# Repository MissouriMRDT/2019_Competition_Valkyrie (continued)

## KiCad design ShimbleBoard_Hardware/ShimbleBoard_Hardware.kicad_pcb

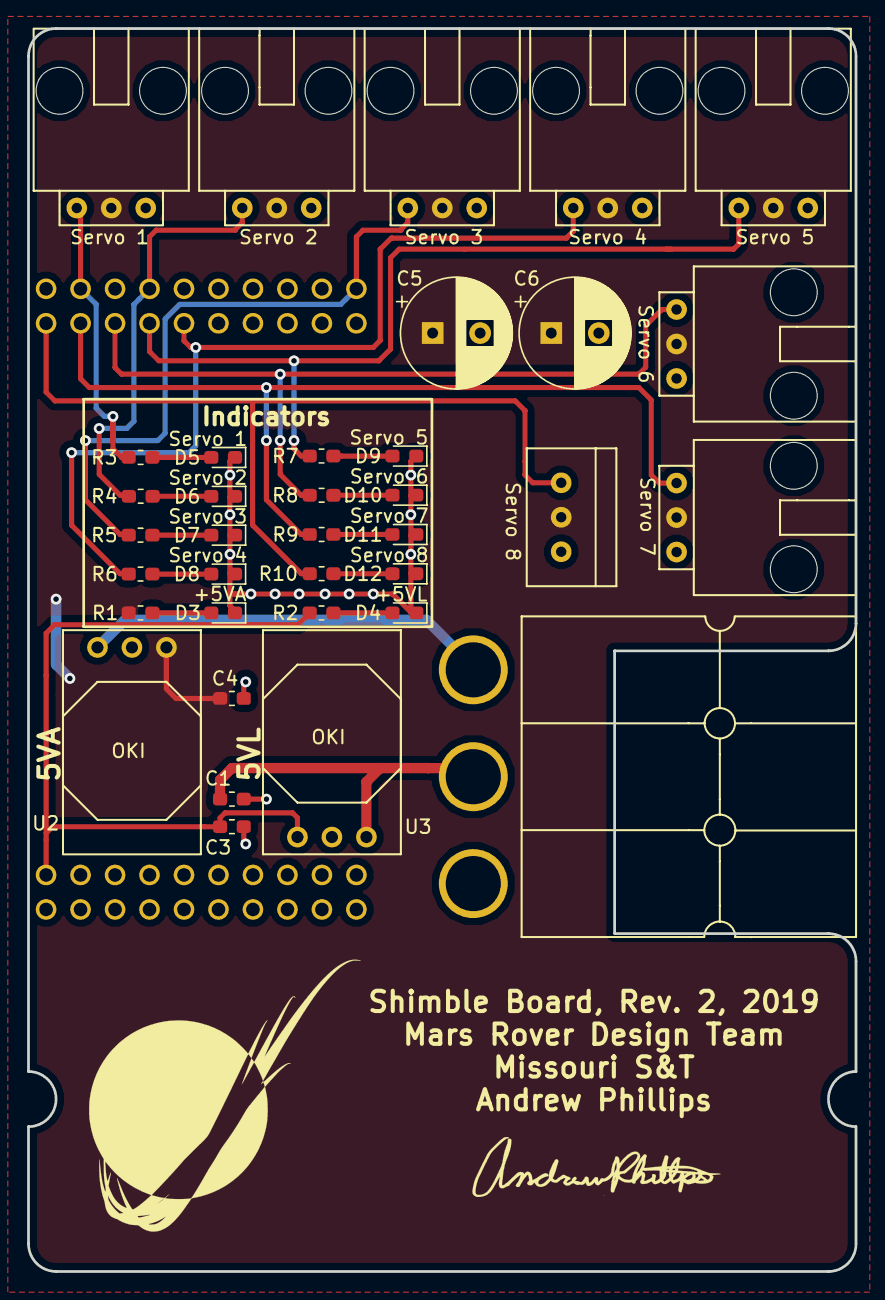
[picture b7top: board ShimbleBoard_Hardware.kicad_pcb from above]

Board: 2 copper layers, 61.0 x 91.6 mm, 38 parts (1 on the bottom side), 23 nets.

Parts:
C1, C2, C3, C4: 10uF; C_0603_1608Metric_Pad1.05x0.95mm_HandSolder
C5, C6: 470u; CP_Radial_D8.0mm_P3.50mm
Conn1: AndersonPP; Anderson_3_Horizontal_Side_by_Side
Conn2, Conn3, Conn4, Conn5, Conn6, Conn7, Conn8: Molex_SL_03; MOLEX_SL_03_Horizontal
Conn9: Molex_SL_03; MOLEX_SL_03_Vertical
D3: 5V_Act_LED; D_0603_1608Metric_Pad1.05x0.95mm_HandSolder
D4: 5V_Log_LED; D_0603_1608Metric_Pad1.05x0.95mm_HandSolder
D5: Ctrl_1_LED; D_0603_1608Metric_Pad1.05x0.95mm_HandSolder
D6: Ctrl_2_LED; D_0603_1608Metric_Pad1.05x0.95mm_HandSolder
D7: Ctrl_3_LED; D_0603_1608Metric_Pad1.05x0.95mm_HandSolder
D8: Ctrl_4_LED; D_0603_1608Metric_Pad1.05x0.95mm_HandSolder
D9: Ctrl_5_LED; D_0603_1608Metric_Pad1.05x0.95mm_HandSolder
D10: Ctrl_6_LED; D_0603_1608Metric_Pad1.05x0.95mm_HandSolder
D11: Ctrl_7_LED; D_0603_1608Metric_Pad1.05x0.95mm_HandSolder
D12: Ctrl_8_LED; D_0603_1608Metric_Pad1.05x0.95mm_HandSolder
R1, R2, R3, R4, R5, R6, R7, R8, R9, R10: 500; R_0603_1608Metric_Pad1.05x0.95mm_HandSolder
U1: TM4C129E_Launchpad; TM4C129E_Launchpad_X7_THT_BOTTOM
U2, U3: OKI; OKI_Horizontal

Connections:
+5VA: C4.1, C5.1, C6.1, Conn2.2, Conn3.2, Conn4.2, Conn5.2, Conn6.2, Conn7.2, Conn8.2, Conn9.2, R1.1, U2.3
+5VL: C3.1, R2.1, U1.+5V', U3.3
+12L: C1.1, Conn1.2, U3.1
+12VA: C2.2, Conn1.3, U2.1
GND: C1.2, C2.1, C3.2, C4.2, C5.2, C6.2, Conn1.1, Conn2.3, Conn3.3, Conn4.3, Conn5.3, Conn6.3, Conn7.3, Conn8.3, Conn9.3, D3.1, D4.1, D5.1, D6.1, D7.1, D8.1, D9.1, D10.1, D11.1, D12.1, U1.GND, U2.2, U3.2
unnamed: D3.2, R1.2
unnamed: D4.2, R2.2
unnamed: D5.2, R3.2
unnamed: D6.2, R4.2
unnamed: D7.2, R5.2
unnamed: D8.2, R6.2
unnamed: D9.2, R7.2
unnamed: D10.2, R8.2
unnamed: D11.2, R9.2
unnamed: D12.2, R10.2
Servo_1_Ctrl: Conn2.1, R3.1, U1.PM7
Servo_2_Ctrl: Conn3.1, R4.1, U1.PA7
Servo_3_Ctrl: Conn4.1, R5.1, U1.PM6
Servo_4_Ctrl: Conn5.1, R6.1, U1.PM1
Servo_5_Ctrl: Conn6.1, R7.1, U1.PM0
Servo_6_Ctrl: Conn7.1, R8.1, U1.PK5
Servo_7_Ctrl: Conn8.1, R9.1, U1.PK4
Servo_8_Ctrl: Conn9.1, R10.1, U1.PG1

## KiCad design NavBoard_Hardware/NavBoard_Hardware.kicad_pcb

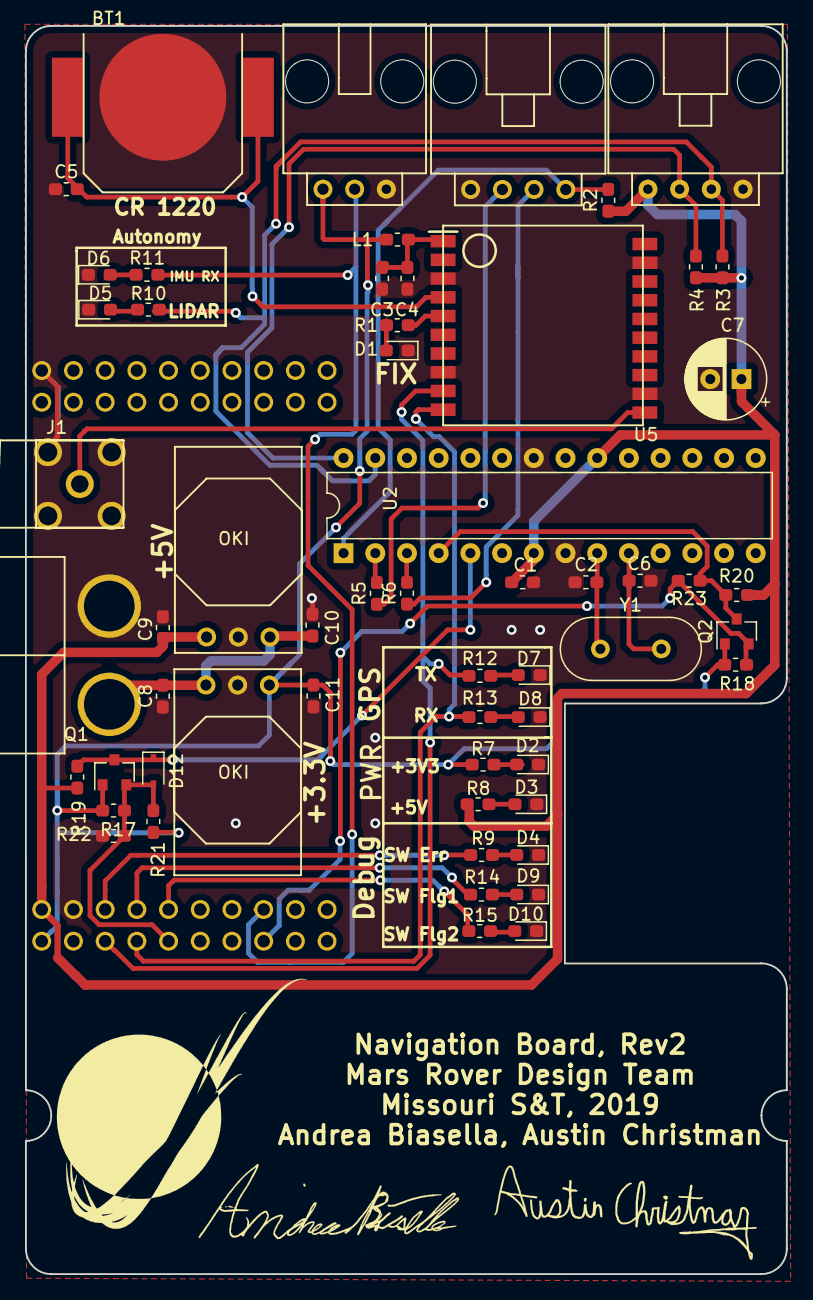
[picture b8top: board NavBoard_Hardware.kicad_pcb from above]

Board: 2 copper layers, 61.0 x 100.0 mm, 59 parts (0 on the bottom side), 37 nets.

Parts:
BT1: Battery_Cell; CR1220_Battery_Holder
C1, C3, C5: 1uF; C_0603_1608Metric_Pad1.05x0.95mm_HandSolder
C2, C6: 22pF; C_0603_1608Metric_Pad1.05x0.95mm_HandSolder
C4: 0.01uF; C_0603_1608Metric_Pad1.05x0.95mm_HandSolder
C7: 680uF; CP_Radial_D6.3mm_P2.50mm
C8, C9, C10, C11: 10u; C_0603_1608Metric_Pad1.05x0.95mm_HandSolder
Conn1: AndersonPP; Anderson_2_Horizontal_Side_by_Side
Conn2: LiDAR; MOLEX_SL_04_Horizontal
Conn3: Molex_SL_03; MOLEX_SL_03_Horizontal
Conn4: Molex_SL_04; MOLEX_SL_04_Horizontal
D1: FIX; LED_0603_1608Metric_Pad1.05x0.95mm_HandSolder
D2, D3, D4, D5, D6, D7, D8, D9, D10: LED; LED_0603_1608Metric_Pad1.05x0.95mm_HandSolder
D12: 1N4148; D_SOD-323
J1: Conn_Coaxial; RP-SMA_Jack_Tru-Hole_Right-Angle
L1: INDUCTOR; L_0603_1608Metric_Pad1.05x0.95mm_HandSolder
Q1, Q2: BSS138; SOT-23
R1, R5, R6: 1K; R_0603_1608Metric_Pad1.05x0.95mm_HandSolder
R2, R17, R18, R19, R20, R21: 10K; R_0603_1608Metric_Pad1.05x0.95mm_HandSolder
R3, R4: 4.7K; R_0603_1608Metric_Pad1.05x0.95mm_HandSolder
R7, R8, R9, R10, R11, R12, R13, R14, R15: 500; R_0603_1608Metric_Pad1.05x0.95mm_HandSolder
R22: 30K; R_0603_1608Metric_Pad1.05x0.95mm_HandSolder
R23: 0; R_0603_1608Metric_Pad1.05x0.95mm_HandSolder
U1: TM4C129E_Launchpad_X9_THT_BOTTOM
U2: ATMEGA328P-Project_Library; DIP-28_W7.62mm
U3, U4: OKI; OKI_Horizontal
U5: FGPMMOPA6H
Y1: Crystal; Crystal_HC49-U_Vertical

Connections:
+3V3: C11.1, Conn3.1, L1.1, Q1.1, Q2.1, R7.1, R17.1, R18.1, R21.1, U1.+3V3, U4.3
+5V: C1.1, C7.1, C9.1, Conn2.1, R2.1, R3.1, R4.2, R8.1, R19.1, R20.1, U1.+5V, U2.7, U2.20, U3.3
/EXAnt: J1.1, U5.11
ATM_RX: Q2.3, R20.2, R23.1, U2.4
ATM_TX: D12.1, Q1.3, R19.2, U2.5
Error_LED: R9.1, U1.PE0
GND: BT1.2, C1.2, C2.2, C3.1, C4.1, C5.2, C6.2, C7.2, C8.2, C9.2, C10.2, C11.2, Conn1.1, Conn2.4, Conn3.3, Conn4.1, D1.1, D2.1, D3.1, D4.1, D5.1, D6.1, D7.1, D8.1, D9.1, D10.1, J1.2, R22.2, U1.GND, U2.8, U2.22, U3.2, U4.2, U5.3, U5.8, U5.12, U5.19
GPS_RX: R12.1, U1.PC4, U5.9
GPS_TX: R13.1, U1.PC5, U5.10
IMU_RX: Conn3.2, R11.1, U1.PA6
LIDAR_SCL: Conn2.2, R4.1, U2.28
LIDAR_SDA: Conn2.3, R3.2, R10.1, U2.27
unnamed: C2.1, U2.9, Y1.1
unnamed: C3.2, C4.2, L1.2, U5.1
unnamed: C6.1, U2.10, Y1.2
unnamed: C8.1, C10.1, Conn1.2, U3.1, U4.1
unnamed: D1.2, R1.2
unnamed: D2.2, R7.2
unnamed: D3.2, R8.2
unnamed: D4.2, R9.2
unnamed: D5.2, R10.2
unnamed: D6.2, R11.2
unnamed: D7.2, R12.2
unnamed: D8.2, R13.2
unnamed: D9.2, R14.2
unnamed: D10.2, R15.2
unnamed: R1.1, U5.5
unnamed: R5.2, U2.2
unnamed: R6.2, U2.3
Programming_RX: Conn4.2, R5.1
Programming_TX: Conn4.3, R6.1
RESET: Conn4.4, R2.2, U2.1
SW_Flg1: R14.1, U1.PE1
SW_Flg2: R15.1, U1.PE2
TIVA_RX: D12.2, Q1.2, R17.2, R21.2, R22.1, U1.PC6
TIVA_TX: Q2.2, R18.2, R23.2, U1.PC7
VBACKUP: BT1.1, C5.1, U5.4

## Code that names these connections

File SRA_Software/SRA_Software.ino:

//Code: Austin Christman
//SRA Software
#include "Adafruit_Sensor.h"
#include "src/DHT/DHT_U.h" //AM2302 Sensor .h files
#include "src/DHT/DHT.h"
#include "src/SHT-XX/SHT1x.h"// SHT-10 Sensor .h files
#include <math.h>


//Rover .h Files
#include "RoveComm.h"
#include "src/Spectrometer/Spectrometer.h"


//pin layout for Tiva C w/ tm4c129
#define SOIL_DATA_PIN          PE_5// Pin located in section X_9:A1, pin PE5
#define CCD_INT_PIN            PE_0// Pin located in section X_9:B1, pin PE0
#define METHANE_VOUT_PIN       PE_2// Pin located in section X_9:B1, pin PE2
#define ATM_DOUT_PIN           PN_2// Pin located in section X_9:D1, pin PN2
#define SW_FLAG1_PIN           PP_4// Pin located in section X_7:A2, pin PP4
#define SW_FLAG2_PIN           PN_5// Pin located in section X_7:A2, pin PN5
#define SW_ERROR_PIN           PN_4// Pin located in section X_7:A2, pin PN4
#define SOIL_SCK_PIN           PB_5// Pin located in seciotn X_7:B2, pin PB5
#define CCD_OS_PIN             A19 // Pin located in section X_7:B2, pin PK3
#define UV_TOGGLE_PIN          PP_5// Pin located in section X_7:D2, pin PP5
#define DHTTYPE                DHT22 // DHT 22 sensor/AM2302 sensor

#define METHANE_ADC_LOW        950 //Value at NewMexico
#define METHANE_ADC_HIGH       1000 
#define METHANE_ACTUAL_LOW     1700 //Average ppb
#define METHANE_ACTUAL_HIGH    1900 //ppb
//#define METHANE_ACTUAL_LOW     1866 //Average ppb
//#define METHANE_ACTUAL_HIGH    970000000 //ppb

int   sensorValue = 0;
uint32_t   methanePpm = 0;
float humidity_atm = 0;
float temperature_atm = 0;
float temperature_soil = 0;
float moisture = 0;


//Rovecomm
RoveCommEthernetUdp Rovecomm;
rovecomm_packet packet;


//delay of 5ms
#define ROVECOMM_DELAY    5

SHT1x th_sensor(SOIL_DATA_PIN, SOIL_SCK_PIN);
DHT dht(ATM_DOUT_PIN, DHTTYPE);

void setup() 
{
  Serial.begin(115200);
  delay(100);
  //Serial.println("Serial Begun");
  Rovecomm.begin(RC_SRASENSORSBOARD_FOURTHOCTET);  // SRA board IP: 138
  delay(ROVECOMM_DELAY);
  //Serial.println("Sensors Begin");
  pinMode(UV_TOGGLE_PIN, OUTPUT);
  pinMode(SW_ERROR_PIN, OUTPUT);
  pinMode(SW_FLAG1_PIN, OUTPUT);
  pinMode(SW_FLAG2_PIN, OUTPUT);

  pinMode(METHANE_VOUT_PIN, INPUT);
  
  //inizalise all output pins outputs and input.
  spectrometerSetup(A19);
  dht.begin();
}

void loop() 
{ 
    
  readAM2302();
  mthnSensorMQ4();
  //  readSHT10();  
  indicateSensorErrorAM2302(humidity_atm, temperature_atm);
  
  uint16_t SRADATA[RC_SRASENSORSBOARD_SENSORDATA_DATACOUNT];
  SRADATA[RC_SRASENSORSBOARD_SENSORDATA_AIRTENTRY]=100*temperature_atm;
  SRADATA[RC_SRASENSORSBOARD_SENSORDATA_AIRMENTRY]=100*humidity_atm;
  SRADATA[RC_SRASENSORSBOARD_SENSORDATA_SOILTENTRY]=1;//100*moisture;
  SRADATA[RC_SRASENSORSBOARD_SENSORDATA_SOILMENTRY]=1;//100*temperature_soil;
  SRADATA[RC_SRASENSORSBOARD_SENSORDATA_METHANEENTRY]= (uint16_t)methanePpm;
  packet = Rovecomm.read();
  Serial.println(".");
  if(packet.data_id!=0)
  {
   
    for(int i=0; i<packet.data_count; i++)
    {
      //Serial.print(packet.data[i]);
    }
    switch(packet.data_id)
    {
      case  RC_SRASENSORSBOARD_UVLEDENABLE_DATAID:
      {
        //Serial.println("UV Toggle");
        toggleUvLed();
        break;
      }
      case RC_SRASENSORSBOARD_SPECTROMETERRUN_DATAID:
      {
        //Serial.println("Spectrometer Running");
        digitalWrite(UV_TOGGLE_PIN, HIGH);
        digitalWrite(SW_FLAG1_PIN, HIGH);
        if(!spectrometerRun(A19, packet.data[0], true)) //True prints data to serial
        {
          digitalWrite(SW_ERROR_PIN, HIGH);
          delay (1000);
          digitalWrite(SW_ERROR_PIN, LOW);
        }
        digitalWrite(SW_FLAG1_PIN, LOW);
        digitalWrite(UV_TOGGLE_PIN, LOW);
      }
    }
  }

  static int timer = 0;

  if(timer > millis()) timer = millis();
  
  if(millis()-timer>=1000)
  {
    bool do_break = false;
    for(int i = 0; i<5; i++)
    {
      Serial.println(SRADATA[i]);
      if(SRADATA[i] == 0) do_break = true;
    }
    if(1)//!do_break)
    {
      Serial.println("Sending//////////////////////////////////////");
      timer = millis();
      Rovecomm.write(RC_SRASENSORSBOARD_SENSORDATA_HEADER, SRADATA);
    }
  }
  
  
  delay(ROVECOMM_DELAY);
}



//SHT-10 Sensor code for soil Temp and Moisture levels 
void readSHT10()
{
  moisture = th_sensor.readHumidity();
  temperature_soil = th_sensor.readTemperatureC();
  Serial.print("Temperature: ");Serial.print(temperature_soil);Serial.print(" C, Humidity: ");Serial.print(moisture);Serial.println(" ");
}



//AM2302 Code for Temp and Humidity.
void readAM2302()
{
  humidity_atm = dht.readHumidity();
  temperature_atm = dht.readTemperature();
  Serial.print(F("Humidity: "));Serial.print(humidity_atm);Serial.print(F("% Temperature: "));Serial.print(temperature_atm);Serial.print(F(" C "));Serial.println((""));
}



//MQ-4 Code for reading Methane Values
void mthnSensorMQ4()
{
  delay(100); //Long delay will slow down code immensly
  uint16_t adc_reading = analogRead(METHANE_VOUT_PIN);
  Serial.print("Methane ADC:");  
  Serial.println(adc_reading);
  methanePpm = adc_reading;//map(adc_reading, METHANE_ADC_LOW, METHANE_ADC_HIGH, METHANE_ACTUAL_LOW, METHANE_ACTUAL_HIGH);//300 - 10,000 are in parts per million.(units)
  constrain(methanePpm, 0, 65535); //to cast to lower unit
  Serial.println("Methane Actual:");
  Serial.println(methanePpm, DEC);
  
}

//Indicates an Error with the SHT-10:
//If flashing most likely cause is connection issues
void indicateSensorErrorSHT10(float moisture, float temperature_soil)
{
  if((isnan(temperature_soil) && isnan(moisture)))
  {
    Serial.println(("Failed to read from the SHT10 sensor!"));
    digitalWrite(SW_ERROR_PIN, HIGH);
    delay (600);
    digitalWrite(SW_ERROR_PIN,LOW);
    delay (300);
    return;
  }
}



//Indicates an error with the AM2302 Sensor.
void indicateSensorErrorAM2302(float humidity_atm, float temperature_atm)
{
  if((isnan(temperature_atm) && isnan(humidity_atm)))
  {
    Serial.println(("Failed to read from the AM2302 sensor!"));
    digitalWrite(SW_ERROR_PIN, HIGH);
    delay (600);
    digitalWrite(SW_ERROR_PIN,LOW);
    delay (300);
    return;
  }
}



//Toggles our UV Led on and off through rovecomm.
void toggleUvLed()
{
  if(packet.data[0] == 1) //RC_SRASENSORSBOARD_UVLEDENABLE_ENABLED)
  {
    digitalWrite(UV_TOGGLE_PIN, HIGH);
  }
  else
  {
    digitalWrite(UV_TOGGLE_PIN, LOW);
  }
}

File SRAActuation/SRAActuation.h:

#ifndef _SRAActuation
#define _SRAActuation

#include "RoveComm.h"
#include "RoveStmVnhPwm.h"

//////Pinouts//////
#define SPECTZ_INA     PL_0
#define SPECTZ_INB     PL_1
#define SPECTZ_PWM     PF_1
#define SPECTZ_HEADER  SPECTZ_INA,SPECTZ_INB,SPECTZ_PWM
                       
#define SPECTX_INA     PL_2
#define SPECTX_INB     PL_3
#define SPECTX_PWM     PF_2
#define SPECTX_HEADER  SPECTX_INA,SPECTX_INB,SPECTX_PWM
                       
#define SPECTY_INA     PQ_2
#define SPECTY_INB     PQ_3
#define SPECTY_PWM     PK_4
#define SPECTY_HEADER  SPECTY_INA,SPECTY_INB,SPECTY_PWM
                       
#define UNUSED_INA     PP_3
#define UNUSED_INB     PQ_1
#define UNUSED_PWM     PG_1
#define UNUSED_HEADER  UNUSED_INA,UNUSED_INB,UNUSED_PWM
 
#define SPECTZ_PB      PG_0
#define SPECTX_PB      PL_4
#define SPECTY_PB      PE_1
#define UNUSED_PB      PE_2

#define DIR_SW PB_3

#define SPECTZ_LOW_LS  PM_5
#define SPECTZ_MID_LS  PM_4
#define SPECTZ_UPP_LS  PA_6
#define SPECTX_CENTER  PD_7
#define LS_5  PC_7
#define LS_6  PD_3
#define LS_7  PE_5
#define LS_8  PC_6

#define SW_IND1 PM_7
#define SW_IND2 PP_5
#define SW_ERR  PA_7

#define BUTTON_SPEED 500

RoveCommEthernetUdp RoveComm;

RoveStmVnhPwm Spectz;
RoveStmVnhPwm Spectx;
RoveStmVnhPwm Specty;

int z_speed;
int x_speed;
int y_speed;

uint8_t current_position;
uint8_t target_position;
uint8_t ls_pressed;

bool do_to_pos_z;
bool ignore_buttons;
bool watchdog_triggered = false;
bool found_x_center = false;

bool x_centered;
bool do_ls = true;
bool center;
int x_pos;

void readRoveComm();
void sendStates();
void checkButtons();
void checkLS();
void writeSpeeds();
void moveToPos();
void adjustX();
void watchdogTriggered();
void clearWatchdog();

#endif

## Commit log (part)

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2014-10-06 Deleted junk files
2014-10-06 Smaller and cleaner
    Switched the headers so I could draw circles around the PWM pins and
    then got the idea to shave 50mill off the width and I forget how much
    off the top. I need to stop.
2014-10-07 Finished review with Jake
    I think it is good to merge back to master
2014-10-14 Finished and ready for fab
    I think unless anyone finds any little thing to change
2014-10-22 Power Board Cleanup and Trace Fixes
    Fixed motor output traces to handle currents as well as removed thermals
    from some parts for e-table.
2014-10-26 Fixed polygon pour overlaps
    Eric fucked up with a ton of pours, so I fixed all of the overlaps, and
    removed more thermal reliefs.
2014-10-27 added .gitignore
    blocks the weird Eagle backup files
2014-10-29 Continued work
    Added lots of stuff
2014-10-31 Continued work
    Added a MOSFet for the primary voltage busses and input terminals
2014-11-04 Added the LT1910 for the MOSFET driver
    Also I copied and pasted all of the primary voltage busses.
2014-11-05 Removed Primary voltage busses
    I was overeager with my copying and pasting. I removed the busses so I
    could keep working on them.
2014-11-05 Pi-Filter, Regulated outputs, and signals
    Added an (unvalued) Pi filter on the output of the 5V critical bus,
    began adding output terminals and LEDs for the regulated outputs, added
    an LED to the unregulated output, fixed values, and connected analog
    signals to the MCU.
2014-11-06 Initial Commit of brd file
    Generated board file.
2014-11-07 Into sex
    is happen
2014-11-07 Speaking of sexual experiences...
    It is bed time. Cleaned up the ugly pour. Work will resume tomorrow.
2014-11-15 Creating a second revision
    Using new parts that were discovered recently
2014-11-16 Updated parts
    Minor changes to symbol for LT1910
2014-11-19 [sexuality intensifies]
    board is down to 95 airwires, 6.6x5.8"
2014-11-19 Added dimensions to the Revision 1 board
2014-11-19 continued arousing myself
2014-11-19 Began routing signal traces
2014-11-20 uh something
2014-11-20 Obligatory joke about sexual arousal
    Also I added space in some of the traces for filtering passives, if
    necessary. will talk to someone who can into EMC.
2014-11-20 Increased sexiness
    Board is now sexier.
2014-11-25 Added Datasheet PDFs
    Datasheets are for all devices on the 2015 board
2014-11-28 Power-Board Dumb-Board Attempt 1
    Removed sensing devices and controllers from schematic, attempted
    routing on board
2014-11-29 Dumb Board - Attempt 2
    Fixed schematic and rerouted
2014-12-02 More Changes
    Removed LED’s and increased V_BATT polygon pour
2014-12-10 Added a solder jumper between VCC and VBUS
2014-12-11 Added poly fuse
2014-12-12 fixed ranking on polygons
2015-01-15 Undid my deleting of the files
    fuck. i don’t know how to anything ever
2015-01-15 Removed ferrite bede on 12V non-critical output
2015-01-17 Fixed DRC Errors for 3oz Copper
    Brought board to spec for 4PCB's 3oz Copper
2015-01-17 Added Bill of Materials
2015-01-18 Added everything but inductor
2015-01-22 Thumb files
2015-01-28 Added new Inductor for Pi Filter ***NEEDS FINISH
    Pi Filter now uses Fair-Rite 2773019447 Inductor.
    THE FOOTPRINT HAS CHANGED! I ONLY HAVE THE LITE VERSION OF EAGLE, SO IT
    IS NOT LAYED OUT PROPERLY YET!!
2015-04-26 DFM revisions
    Working on preparing the board for a new print.
2015-05-01 Experimental changes
2015-05-03 Finished board for order and made gerbers
2015-05-23 Added Spences Powerboard folder
2015-12-15 Added final components and started routing.
2015-12-15 Continued routing.
2016-01-05 Minor routing changes
2016-01-12 Rearranged some routing for better ground flow.
2016-01-13 swapped high current horiz o/p for vert, edited other rj45 connection
2016-01-13 added top gnd plane, moved high current connectors, gen dxf
2016-01-14 removed text in tstop
2016-01-15 Swapped Individual APP terminals for 2-pos.
2016-01-15 Updated .dfx
2016-01-15 Deleted Unnecessary Polygons
2016-01-16 added tiva-c-connected mounting holes
2016-10-01 Power Board 2017 Rev1
    PB layout (just about)complete and ready for review once I add fuses to
    the 12V buses.
2016-10-05 Swapped SL connectors, added APP spacer
    Swapped 4-pin Molex SL for two 3-pin SL connectors, added mounting wing
    between power inputs, added board description and MRDT logo, moved big
    caps around
2016-10-05 Added fuse blocks and bus bar mounting holes
    Fuse blocks for the 12V buses. Swapped temporary anderson connectors
    with holes to mount bus bars to connect PB to patch panel.
2016-10-07 Spaced Out Motor Busses
    Components for motor busses are more spread out and more solderable.
2016-10-09 Added Fan Power/Control
2016-10-10 Half duplex RS485, single 5-pin SL connector on left side
2016-10-12 Swapped MAX3077 for MAX3078
2016-10-14 Fixed first board review issues
    - FET for PVDD LED
    - Widened input voltage polygon
    - Added 15V zener on FET gates
    - Added test points
    - Added pull ups on hall-effect lines
    - Added filter on PWM input
2016-10-15 Placed Component Names on Board
2016-10-17 Fixed board review #2 issues
    - Increased polygon isolation
    - Removed hall effect buffer and added RC filters on hall effect lines
    - Added ground vias around driver backplate
2016-10-21 Changed net flag sizes, rerouted some things
2016-10-22 Completed All Changes Adressed in Board Review
2016-10-23 Ready for dat third review
2016-10-23 Switched to MAX232
2016-10-24 Moved GND via above R31 0.01" to left, re-ratsnested
2016-11-28 Fixed Logic and Com Buss Switching
    Rerouted power to the fet drivers so the com and logic busses can be
    properly switched. Also moved fan power to left of standoff, increased
    isolation on converter pins, and rounded corners of board.
2016-12-08 Changed to 4 layers
    UpperMid - power in
    LowerMid - GND
2016-12-08 Moved FETS further from board edge
2016-12-09 Improved routing
    Mainly fault lines
2017-01-13 Wire fixed to right angle
2017-09-19 Power Board 2018 Rev1
    Directly copied from Power Board 2017
2017-09-28 Integrated TIVA added, New Logic bus started
2017-11-04 Custom buck converter finished
    Left to do: via stitch buck converter, route rest of tiva signals, place rs232 comm unit
2017-11-06 Small tweaks
    Rearranged logic bus components to line anderson up with the other buses. Ethernet jack rotated. Mounting holes lined up, corners rounded. Patch panel mounting holes added
2017-11-09 FINAL REV 1 TO BE ORDERED
    Made ground plane around buck converter 4 layers. Adjusted via stitch to allow 3.3v plane to have a larger bottleneck. Flipped logic and comm bus locations. Added + and - near battery terminals. Renu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
2018-03-12 Rev 2 2018
    Integrated tiva/ buck converter removed. Pack voltage arm bus added. Positive and negative terminals flipped. Could add pin receptacles to muratas still
2018-03-14 Arm and Science Bus Text Change
2018-04-17 layout ready to run traces
2018-04-22 Swapped position of Power andersons and Drive board SL
2018-05-17 Added BOM
2018-05-17 Removed Libraries
2018-05-24 Hardware Testing
2018-05-29 switched rovecomm to new rovewareEnergia ver
2018-06-02 changed pins out
2018-09-27 All sections completed except for TIVA Header connections.
2018-09-28 Changed NSCS and serial receive flag locations, started development on second motor controller circuit
2018-10-01 Updated Schematic
    Added power filtering, logic andersons, communication andersons, and general power is a works in progress. This is simply a copy of the schematic from eagle to kicad.
2018-10-04 Added Tiva Headers
    I added Tiva Headers, a full booster and finished the Logic/Communication/Actuation circuit from direct battery power.
2018-10-06 Updated labelings on Schematic
    Got rid of data section of schematic. Made labels bigger and prettier for the schematic for ease of viewing.
2018-10-13 Cleaned up ground connections, fixed an issue with the device library directory paths
2018-10-14 Reorganized schematic structure, fixed the TIVA headers, added dual serial TX and RX for both motors to the MAX3232 and the headers
2018-10-20 Update sym-lib-table
2018-10-20 Added resistor value for pack voltage LED, fixed some formatting for wiring, removed bus connections and replaced with flags (we're going to move to bus connections after PDR)
2018-10-20 Fixed C2000 headers
2018-10-20 Completed Netlist
    Netlist is complete, possible errors to be fixed in next commit. The schematic is finalized, only flags need correction. Updated Schematic FIles for DC-DC Buck Converter. Created obsolete Fuse Block.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
2018-10-21 Fixed netlist naming for GND
2018-10-21 Modified layout
2018-10-22 Reassigned Libraries
    Reassigned Libraries to make sure everything works after file organization.
2018-10-25 1st Placement is complete
    The first placement is now complete, traces still need to be added. The schematic was updated with the placement of Andersons. Certain andersons were in the wrong areas on the schematic. Silkscreen o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
2018-10-26 Added Connections File
    Just an outgoing and incoming signals file.
2018-10-27 Added Signal Type to Pin Map
2018-10-31 Routing Finished
    Routing is now complete for the entire board. Board has passed DRC. Adjusted Silkscreen on board, and removed 5V signal from schematic because it was not contributing anything.
2018-11-11 New general layout completed
    New placement for all components
2018-11-18 Signal and Power Traces Routed
    All signal and Big Power traces have been placed. Added lots of power trace polygons. Replaced drill holes with corner drill holes.
2018-11-21 Camera Board rev 1 schematic
2018-11-25 Almost done with half of the board
2018-11-25 Silkscreen Added
    Silkscreen was added and completed
2018-11-25 cleaned up layout
2018-11-29 Added Extra Documentation and Finished Layout and ready for final review
    Documentation of the libraries required for this project were added. The layout is now finished and updtated from the last review. It is now ready for another review. After next review a BOM will be 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
2018-11-30 routed transient protection
2018-12-01 Updated ToDo.txt
2018-12-01 final touches
2018-12-01 Fixed ground connections
2018-12-01 Minor routing clean up
2018-12-01 Schematic changes
2018-12-02 saved sch
2018-12-08 fixed file naming
2018-12-08 CDR Schemati Changes
2018-12-09 silkscreen touchups
2018-12-12 Completed schematic changes from PDR, currently partway through layout changes. Uploading progress, details listed in the PDR Notes documentation with marks for each item completed
2018-12-12 Placed hardware files in cameraboard_hardware folder
2018-12-13 Swapped Placment of Comm & Logic Busses
2018-12-13 Added BOM, added LED for +5V power
2018-12-14 Added text nest to LEDs
2018-12-14 Replaced +12V labels with power flags
2018-12-14 Added NC to TIVA
2018-12-14 finished silkscreen.
2018-12-14 Added Pinout text
2018-12-15 Updated power conversion.
2018-12-16 Added a BOM and Updated Capacitor Size
    Added a BOM file in the Documentation file. Currently has 2 placeholder values in it due to unknown anderson powerpole colors. Updated the 330u capacitor package to fit a real capacitor.
2018-12-16 Created BOM
2018-12-17 Finished BOM
2018-12-17 made Gerbs
2018-12-18 Created Gerbs
2018-12-23 made schematic
2018-12-28 Organized, changed text, etc
2018-12-28 very small changes
2018-12-29 added questions
2018-12-31 Added Readme
2018-12-31 Revert "sch fixes concerning tiva, leds, pot"
    This reverts commit 363e6566fbd52631f7baef9837a720d31ec6d202.
2018-12-31 i added a singular flag
2019-01-02 cleaned repo
2019-01-17 Updated to KiCAD libraries Rev 2
2019-01-30 Removed Duplicate Parts and Replaced Mousser Comps with Digikey
2019-03-01 Squeezed board even more
    The board is now about 10 inches wide and the board now has a much tighter fit.
2019-03-01 Completed Board Review. Minor Changes to Motor Bus Layout
    Deleted Motor 7 from Board. Renamed Motors 1-6 for other uses and easier reading. Auxillary is now on the right hand side of the board, As well as non motor busses. Front Middle, Back and Extra are a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
2019-03-04 Updated Silkscreen
2019-03-04 Renamed PowerBoard_Hardware FOlder
2019-03-05 Got rid of old BOM, updated new BOM
2019-04-02 created schematic
2019-04-02 Layout
2019-07-09 added git merge with history example
